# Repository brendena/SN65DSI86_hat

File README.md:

# dev board DSI to eDP

Changes

V1.1 - added a external clock, routed test to ground

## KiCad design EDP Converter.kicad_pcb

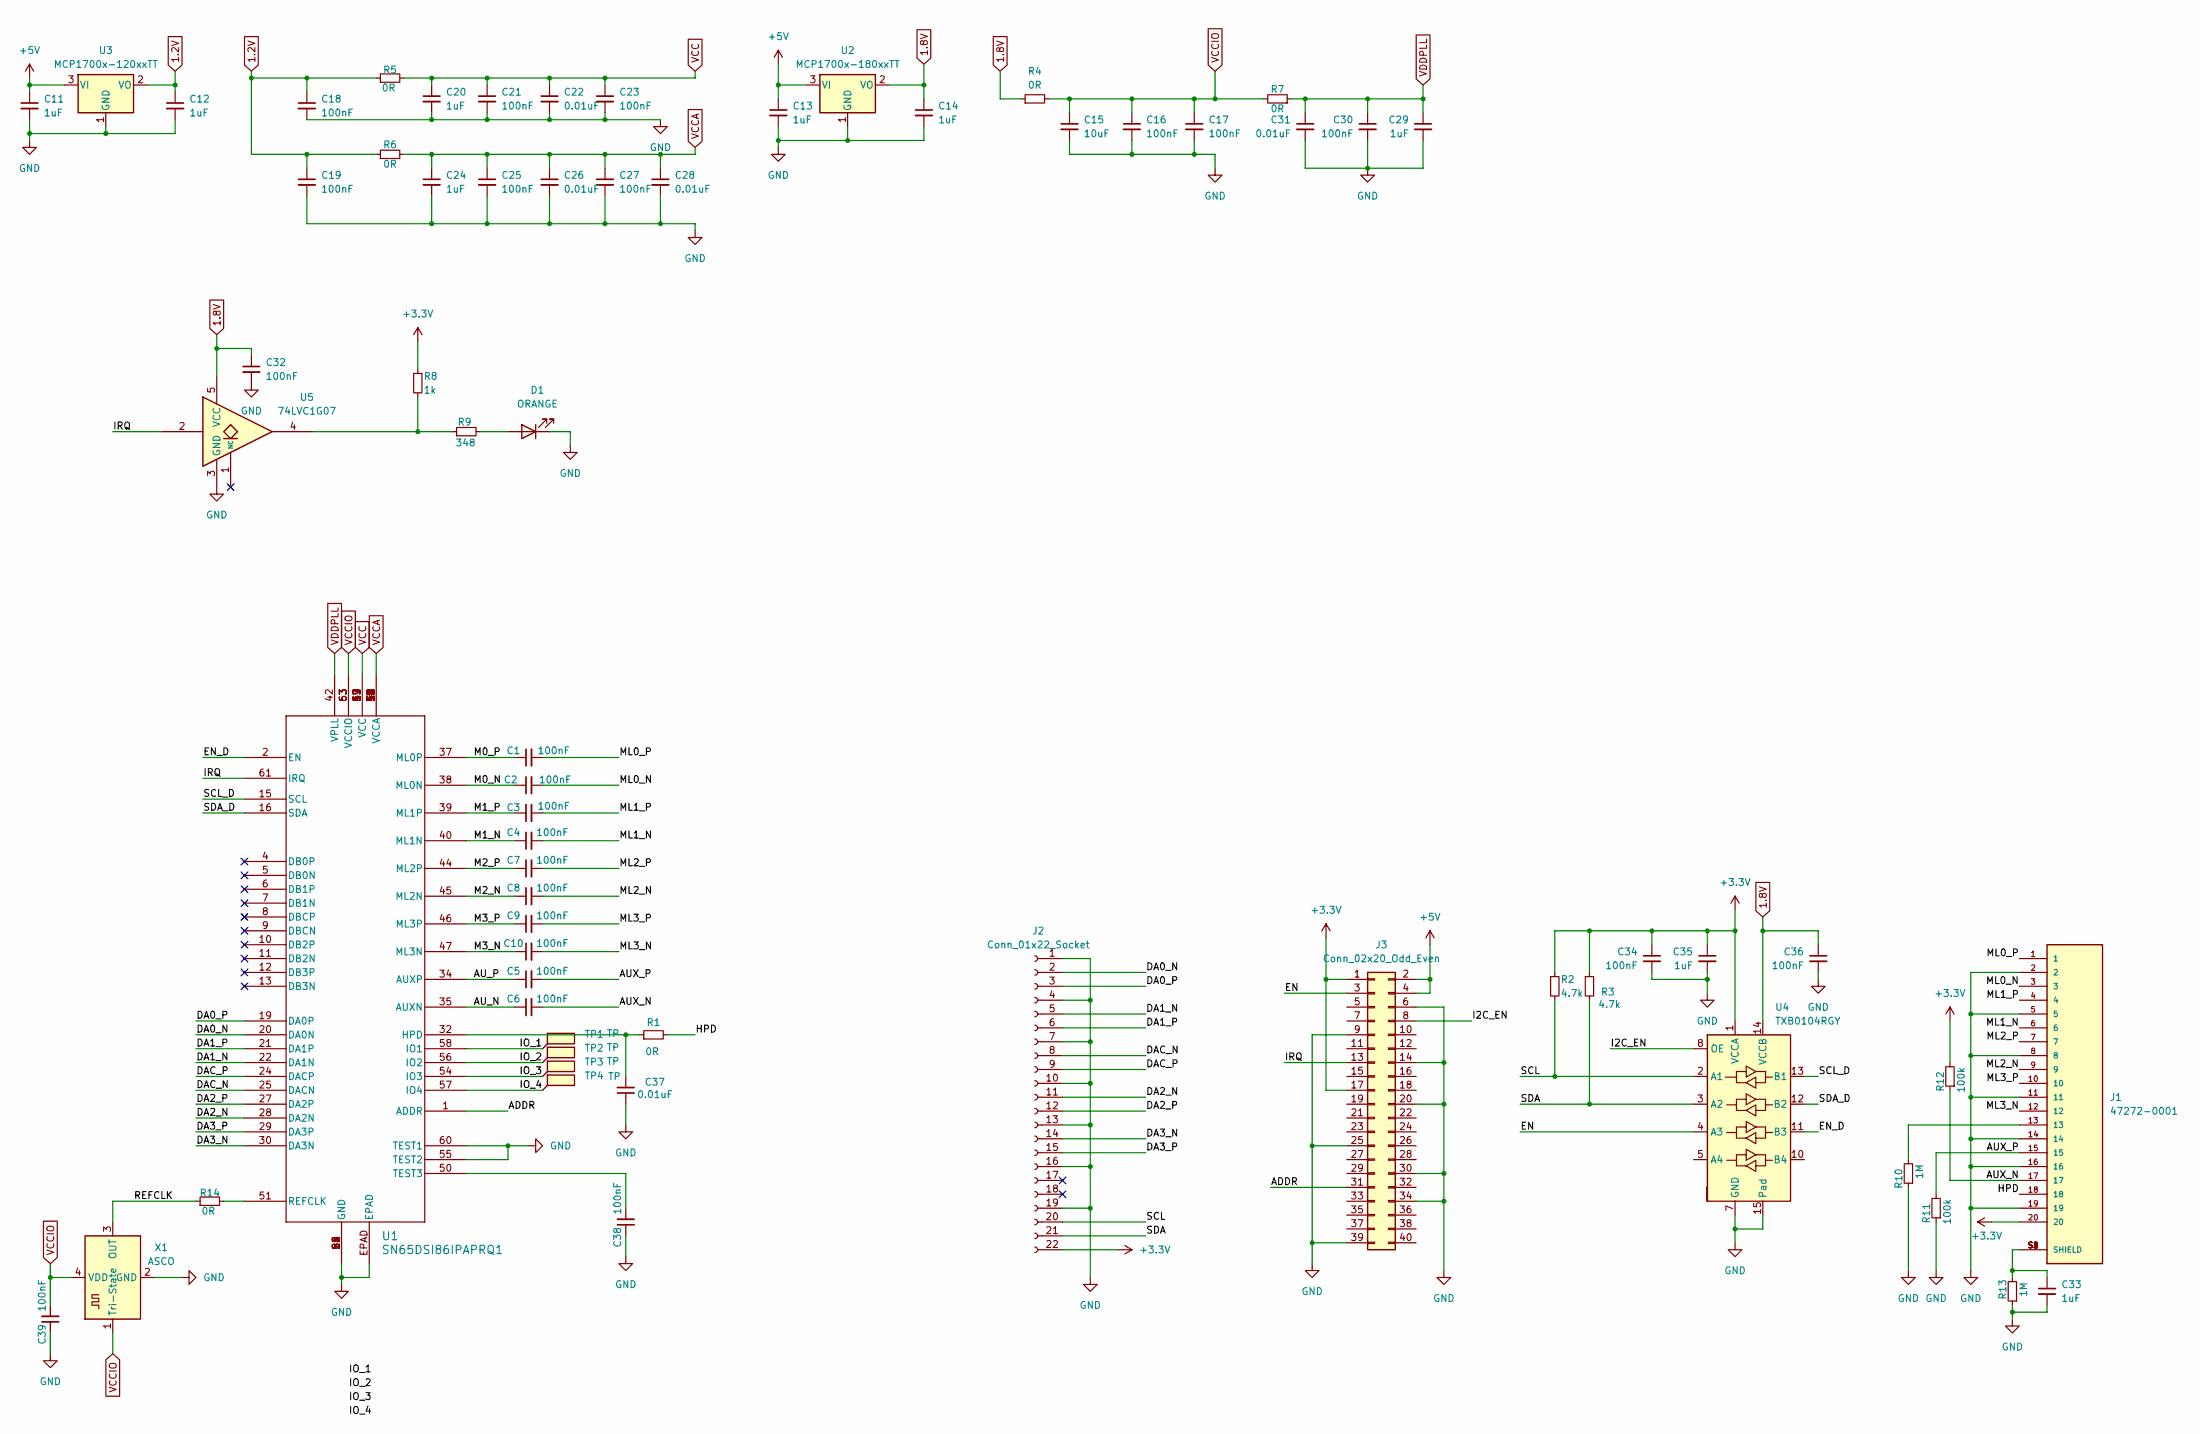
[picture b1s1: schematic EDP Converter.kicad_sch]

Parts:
C1, C2, C3, C4, C5, C6, C7, C8, C9, C10, C16, C17, C18, C19, C21, C23, C25, C27, C30, C32, C34, C36, C38, C39: 100nF; C_0402_1005Metric; MPN CL05B104KP5NNNC
C11, C12, C13, C14, C20, C24, C29, C33, C35: 1uF; C_0402_1005Metric; MPN CL05A105KO5NNNC
C15: 10uF; C_0603_1608Metric; MPN GRM188R61A106ME69D
C22, C26, C28, C31, C37: 0.01uF; C_0402_1005Metric; MPN GRM155R71C103KA01D
D1: ORANGE; LED_0402_1005Metric; MPN XZMOK68W-2
J1: 47272-0001; MOLEX_47272-0001; MPN 0472720001; DigiKey_Part_Number WM19271TR-ND
J2: Conn_01x22_Socket; TE_2-1734839-2_1x22-1MP_P0.5mm_Horizontal; MPN 2-1734839-2 / FH12-22S-0.5SH(55)
J3: Conn_02x20_Odd_Even; PinSocket_2x20_P2.54mm_Vertical; MPN SFH11-PBPC-D20-ST-BK
R1, R4, R5, R6, R7, R14: 0R; R_0402_1005Metric; MPN RC1005J000CS
R2, R3: 4.7k; R_0402_1005Metric; MPN RC0402JR-074K7L
R8: 1k; R_0402_1005Metric; MPN RC0402JR-071KL
R9: 348; R_0402_1005Metric; MPN ERJ-2RKF3480X
R10, R13: 1M; R_0402_1005Metric; MPN ERJ-2RKF1004X
R11, R12: 100k; R_0402_1005Metric; MPN RC0402FR-07100KL
TP1, TP2, TP3, TP4: TP; TestPoint_Pad_2.0x2.0mm
U1: SN65DSI86IPAPRQ1; ZQE64_TEX; MPN SN65DSI86IPAPRQ1
U2: MCP1700x-180xxTT; SOT-23; MPN MCP1700T-1802E/TT
U3: MCP1700x-120xxTT; SOT-23; MPN MCP1700T-1202E/TT
U4: TXB0104RGY; Texas_S-PVQFN-N14; MPN TXB0104RGYR
U5: 74LVC1G07; SOT-353_SC-70-5; MPN SN74LVC1G07DCKR
X1: ASCO; Oscillator_SMD_Abracon_ASCO-4Pin_1.6x1.2mm; MPN ASCO2-27.000MHZ-EK-T3

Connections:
1.2V: C12.1, C18.1, C19.1, R5.1, R6.1, U3.2 (VO)
1.8V: C14.1, C32.1, C36.1, R4.1, U2.2 (VO), U4.14 (VCCB), U5.5 (VCC)
+3.3V: C34.1, C35.1, J1.20, J2.22, J3.1, J3.17, R2.1, R3.1, R8.1, R12.2, U4.1 (VCCA)
+5V: C11.1, C13.1, J3.2, J3.4, U2.3 (VI), U3.3 (VI)
/ADDR: J3.31, U1.1 (ADDR)
/AUX_N: C6.2, J1.17, R12.1
/AUX_P: C5.2, J1.15, R11.2
/AU_N: C6.1, U1.35 (AUXN)
/AU_P: C5.1, U1.34 (AUXP)
/DA0_N: J2.2, U1.20 (DA0N)
/DA0_P: J2.3, U1.19 (DA0P)
/DA1_N: J2.5, U1.22 (DA1N)
/DA1_P: J2.6, U1.21 (DA1P)
/DA2_N: J2.11, U1.28 (DA2N)
/DA2_P: J2.12, U1.27 (DA2P)
/DA3_N: J2.14, U1.30 (DA3N)
/DA3_P: J2.15, U1.29 (DA3P)
/DAC_N: J2.8, U1.25 (DACN)
/DAC_P: J2.9, U1.24 (DACP)
/EN: J3.3, U4.4 (A3)
/EN_D: U1.2 (EN), U4.11 (B3)
/HPD: J1.18, R1.2
/I2C_EN: J3.8, U4.8 (OE)
/IO_1: TP1.1, U1.58 (IO1)
/IO_2: TP2.1, U1.56 (IO2)
/IO_3: TP3.1, U1.54 (IO3)
/IO_4: TP4.1, U1.57 (IO4)
/IRQ: J3.13, U1.61 (IRQ), U5.2
/M0_N: C2.1, U1.38 (ML0N)
/M0_P: C1.1, U1.37 (ML0P)
/M1_N: C4.1, U1.40 (ML1N)
/M1_P: C3.1, U1.39 (ML1P)
/M2_N: C8.1, U1.45 (ML2N)
/M2_P: C7.1, U1.44 (ML2P)
/M3_N: C10.1, U1.47 (ML3N)
/M3_P: C9.1, U1.46 (ML3P)
/ML0_N: C2.2, J1.3
/ML0_P: C1.2, J1.1
/ML1_N: C4.2, J1.6
/ML1_P: C3.2, J1.4
/ML2_N: C8.2, J1.9
/ML2_P: C7.2, J1.7
/ML3_N: C10.2, J1.12
/ML3_P: C9.2, J1.10
/REFCLK: R14.1, X1.3 (OUT)
/SCL: J2.20, R2.2, U4.2 (A1)
/SCL_D: U1.15 (SCL), U4.13 (B1)
/SDA: J2.21, R3.2, U4.3 (A2)
/SDA_D: U1.16 (SDA), U4.12 (B2)
GND: C11.2, C12.2, C13.2, C14.2, C15.2, C16.2, C17.2, C18.2, C19.2, C20.2, C21.2, C22.2, C23.2, C24.2, C25.2, C26.2, C27.2, C28.2, C29.2, C30.2, C31.2, C32.2, C33.2, C34.2, C35.2, C36.2, C37.1, C38.1, C39.1, D1.1 (K), J1.2, J1.5, J1.8, J1.11, J1.14, J1.16, J1.19, J2.1, J2.4, J2.7, J2.10, J2.13, J2.16, J2.19, J3.6, J3.9, J3.14, J3.20, J3.25, J3.30, J3.34, J3.39, R10.1, R11.1, R13.1, U1.23 (GND), U1.26 (GND), U1.52 (GND), U1.55 (TEST2), U1.60 (TEST1), U1.64 (GND), U1.EPAD, U2.1 (GND), U3.1 (GND), U4.7 (GND), U4.15 (Pad), U5.3 (GND), X1.2 (GND)
unnamed: C33.1, J1.S1 (SHIELD), J1.S2 (SHIELD), J1.S3 (SHIELD), J1.S4 (SHIELD), R13.2
unnamed: D1.2 (A), R9.2
unnamed: J1.13, R10.2
unnamed: R8.2, R9.1, U5.4
unnamed: C37.2, R1.1, U1.32 (HPD)
unnamed: R14.2, U1.51 (REFCLK)
unnamed: C38.2, U1.50 (TEST3)
VCC: C20.1, C21.1, C22.1, C23.1, R5.2, U1.17 (VCC), U1.33 (VCC), U1.49 (VCC), U1.59 (VCC), U1.62 (VCC)
VCCA: C24.1, C25.1, C26.1, C27.1, C28.1, R6.2, U1.3 (VCCA), U1.14 (VCCA), U1.18 (VCCA), U1.31 (VCCA), U1.36 (VCCA), U1.41 (VCCA), U1.43 (VCCA), U1.48 (VCCA)
VCCIO: C15.1, C16.1, C17.1, C39.2, R4.2, R7.2, U1.53 (VCCIO), U1.63 (VCCIO), X1.1 (Tri-State), X1.4 (VDD)
VDDPLL: C29.1, C30.1, C31.1, R7.1, U1.42 (VPLL)

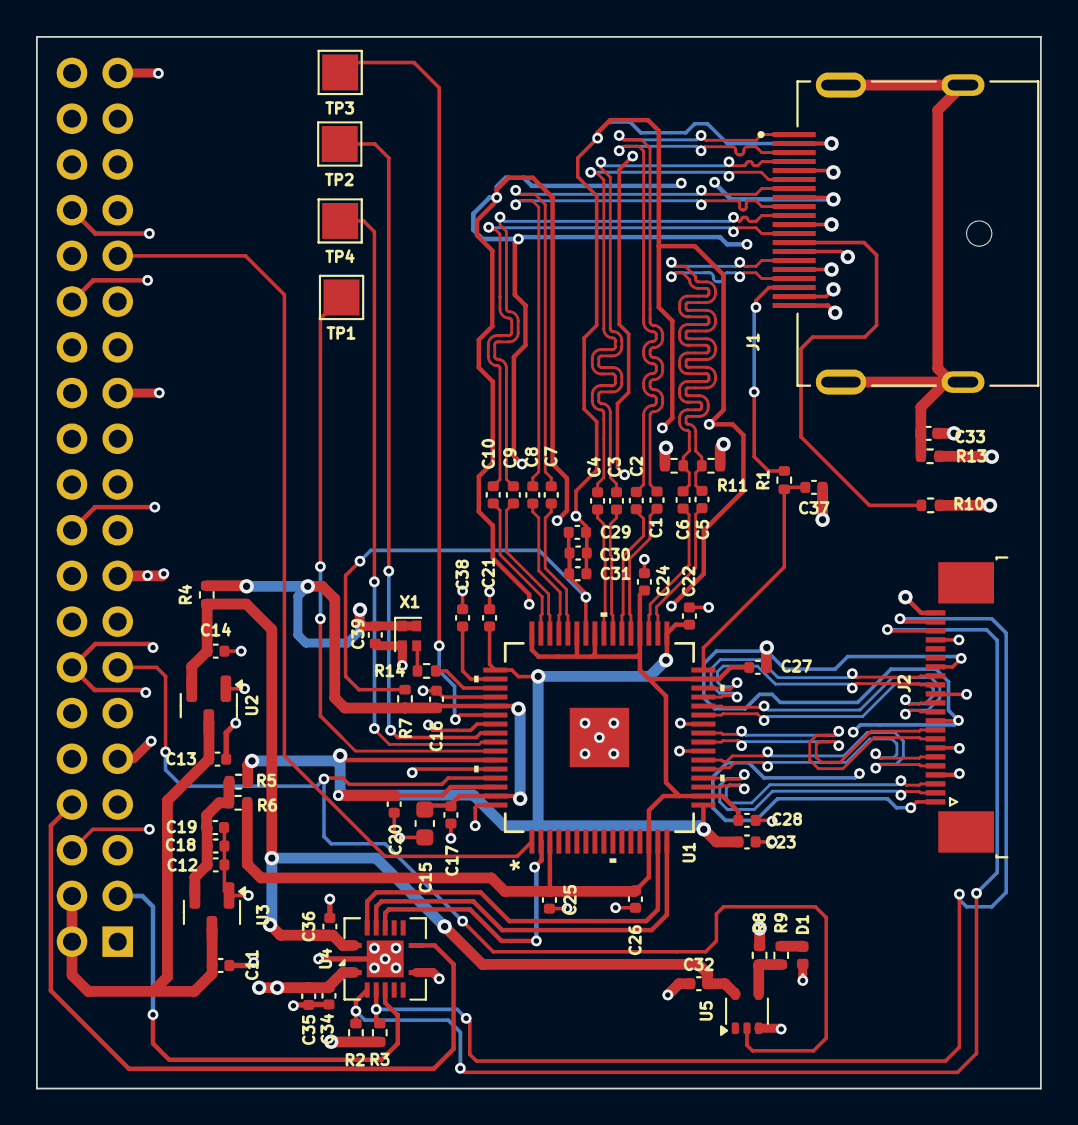
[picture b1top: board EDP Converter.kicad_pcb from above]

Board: 4 copper layers, 55.8 x 58.4 mm, 67 parts (1 on the bottom side), 61 nets.

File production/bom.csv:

Designator,Footprint,Quantity,Value,LCSC Part #
"C1, C10, C16, C17, C18, C19, C2, C21, C23, C25, C27, C3, C30, C32, C34, C36, C38, C39, C4, C5, C6, C7, C8, C9",0402,24,100nF,CL05B104KP5NNNC
"C11, C12, C13, C14, C20, C24, C29, C33, C35",0402,9,1uF,CL05A105KO5NNNC
C15,0603,1,10uF,GRM188R61A106ME69D
"C22, C26, C28, C31, C37",0402,5,0.01uF,GRM155R71C103KA01D
D1,0402,1,ORANGE,XZMOK68W-2
J1,MOLEX_47272-0001,1,47272-0001,0472720001
J2,TE_2-1734839-2_1x22-1MP_P0.5mm_Horizontal,1,Conn_01x22_Socket,2-1734839-2 / FH12-22S-0.5SH(55)
J3,PinSocket_2x20_P2.54mm_Vertical,1,Conn_02x20_Odd_Even,SFH11-PBPC-D20-ST-BK
"R1, R14, R4, R5, R6, R7",0402,6,0R,RC1005J000CS
"R10, R13",0402,2,1M,ERJ-2RKF1004X
"R11, R12",0402,2,100k,RC0402FR-07100KL
"R2, R3",0402,2,4.7k,RC0402JR-074K7L
R8,0402,1,1k,RC0402JR-071KL
R9,0402,1,348,ERJ-2RKF3480X
U1,ZQE64_TEX,1,SN65DSI86IPAPRQ1,SN65DSI86IPAPRQ1
U2,SOT-23,1,MCP1700x-180xxTT,MCP1700T-1802E/TT
U3,SOT-23,1,MCP1700x-120xxTT,MCP1700T-1202E/TT
U4,Texas_S-PVQFN-N14,1,TXB0104RGY,TXB0104RGYR
U5,SOT-353_SC-70-5,1,74LVC1G07,SN74LVC1G07DCKR
X1,Oscillator_SMD_Abracon_ASCO-4Pin_1.6x1.2mm,1,ASCO,ASCO2-27.000MHZ-EK-T3

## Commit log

2024-05-18 first itteration
2024-05-18 added image
2024-06-01 added the v1.1 which few modifications
